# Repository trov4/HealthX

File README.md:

# HealthX
The Health X repository storing all code for the project

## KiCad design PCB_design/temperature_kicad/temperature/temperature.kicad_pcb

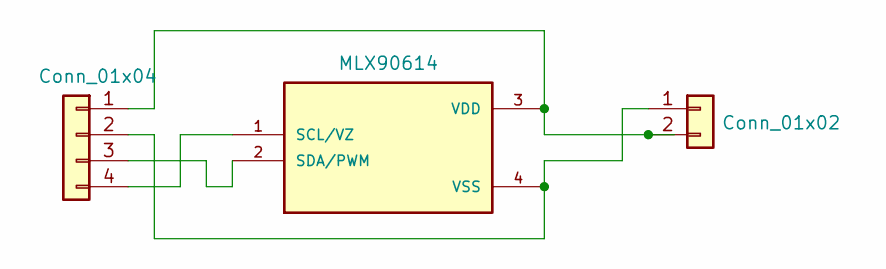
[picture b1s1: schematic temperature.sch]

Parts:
J1: Conn_01x04; PinHeader_1x04_P2.54mm_Vertical
J2: Conn_01x02; PinHeader_1x02_P2.54mm_Vertical
U1: MLX90614; TO254P942H425-4; PARTREV 13

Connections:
unnamed: J1.1, J2.2, U1.3 (VDD)
unnamed: J1.2, J2.1, U1.4 (VSS)
unnamed: J1.3, U1.2 (SDA/PWM)
unnamed: J1.4, U1.1 (SCL/VZ)

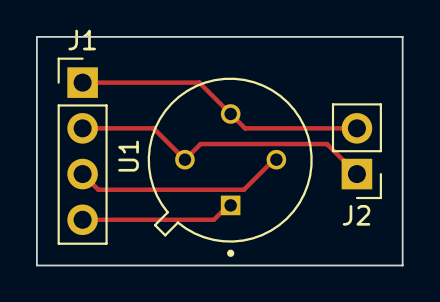
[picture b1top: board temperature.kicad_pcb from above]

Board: 2 copper layers, 20.3 x 12.7 mm, 3 parts (0 on the bottom side), 4 nets.

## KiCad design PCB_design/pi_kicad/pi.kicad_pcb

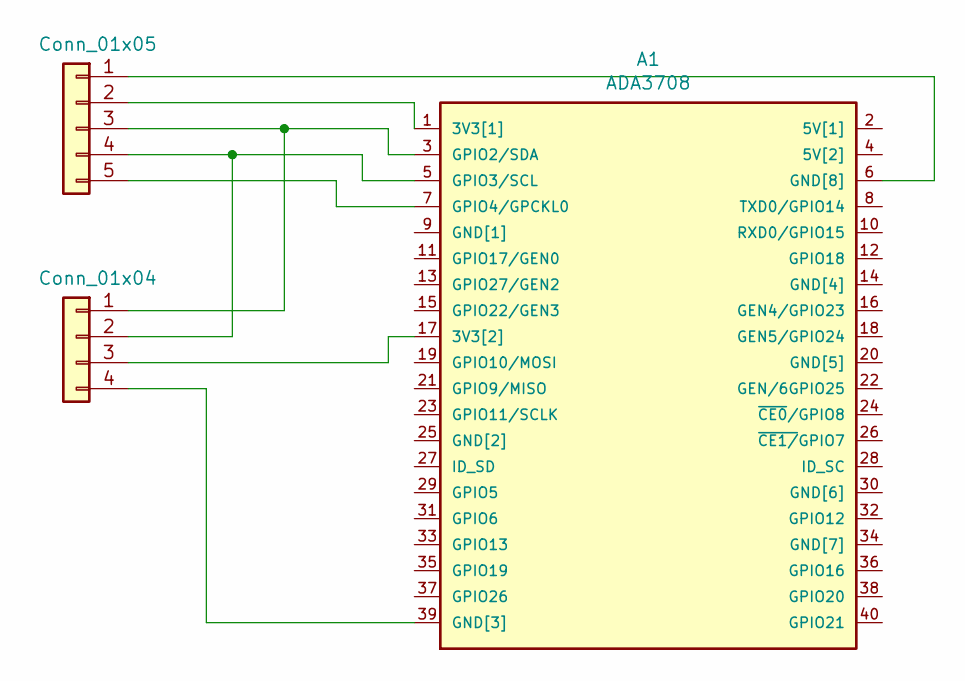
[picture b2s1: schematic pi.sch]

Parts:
A1: ADA3708; ADA3708_RPI-ZERO
J1: Conn_01x05; PinHeader_1x05_P2.54mm_Vertical
J2: Conn_01x04; PinHeader_1x04_P2.54mm_Vertical

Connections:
unnamed: A1.1 (3V3[1]), J1.2
unnamed: A1.3 (GPIO2/SDA), J1.3, J2.1
unnamed: A1.5 (GPIO3/SCL), J1.4, J2.2
unnamed: A1.6 (GND[8]), J1.1
unnamed: A1.7 (GPIO4/GPCKL0), J1.5
unnamed: A1.17 (3V3[2]), J2.3
unnamed: A1.39 (GND[3]), J2.4

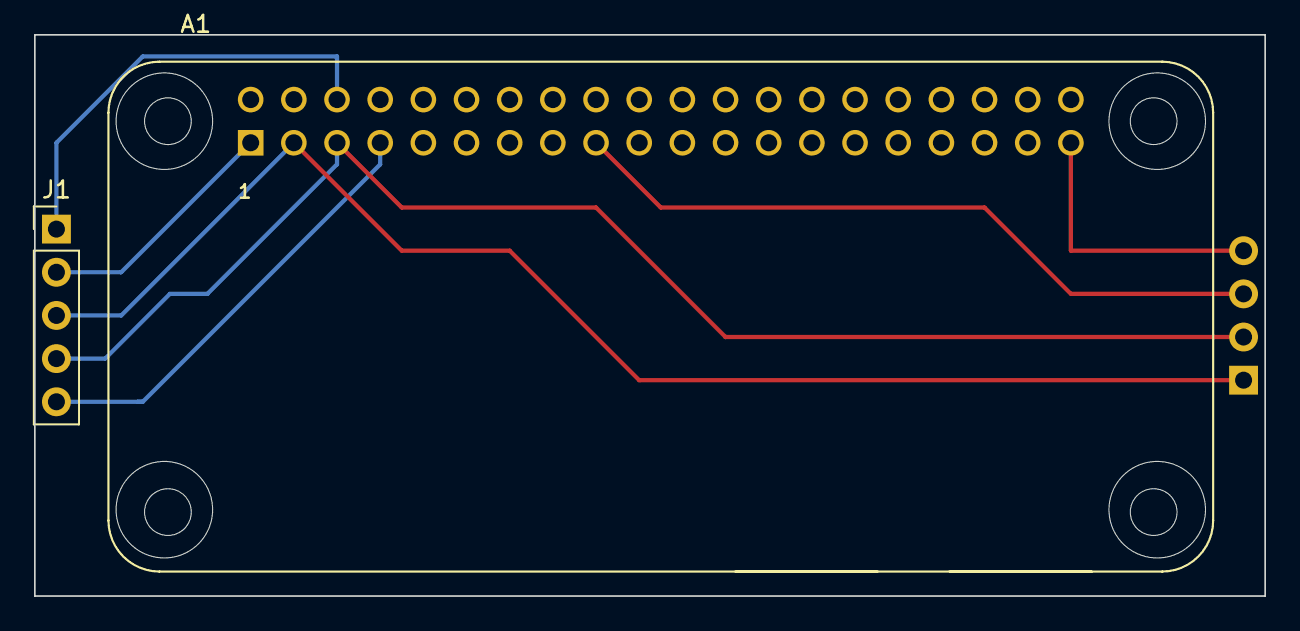
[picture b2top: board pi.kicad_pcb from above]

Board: 2 copper layers, 72.4 x 33.0 mm, 3 parts (1 on the bottom side), 7 nets.

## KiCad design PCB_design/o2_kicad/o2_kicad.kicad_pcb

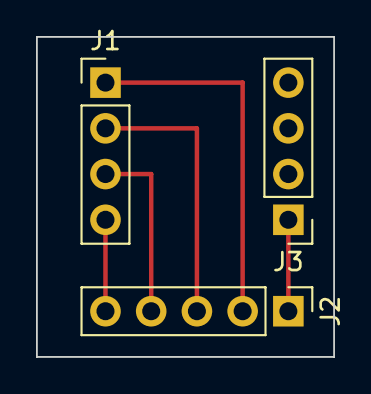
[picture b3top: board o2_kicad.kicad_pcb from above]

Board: 2 copper layers, 16.5 x 17.8 mm, 3 parts (0 on the bottom side), 5 nets.

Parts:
J1, J3: Conn_01x04; PinHeader_1x04_P2.54mm_Vertical
J2: Conn_01x05; PinHeader_1x05_P2.54mm_Vertical

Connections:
unnamed: J1.1, J2.2
unnamed: J1.2, J2.3
unnamed: J1.3, J2.4
unnamed: J1.4, J2.5
unnamed: J2.1, J3.1

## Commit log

2021-08-26 Initialize project using Create React App
2021-09-16 Create info_getItem
2021-09-16 Create info_deleteItem
2021-09-16 Create info_putItem
2021-09-16 Create sensor_getItem
2021-09-16 Create raspberry_pi local
2021-09-21 Create MQTT Connection
2021-09-21 Rename MQTT Connection to AWS IoT
2021-09-23 added David's sensor work
2021-09-23 ahhhh
2021-09-23 removed testing
2021-09-28 This is my commit message
2021-09-30 adding temp sense stuff
2021-10-07 Create GET API
2021-10-14 moving to pi 0
2021-10-14 changing diretory name
2021-10-14 added new IoT to sensors directory
2021-10-14 packed everything up for iot sending
2021-10-15 New version
2021-10-15 adding pymlx items
2021-10-15 This one Trevor
2021-10-15 This one two
2021-10-18 Update GET API
2021-10-28 This is my most recent version
2021-10-28 added rfid submodule
2021-10-28 bump rfid
2021-10-28 This is cert
2021-10-28 IoT updates: RFID connected to AWS
2021-11-16 bump gen2
2021-11-18 The data check done
2021-12-09 Update and rename sensor_getItem to sensor_get_func
2021-12-09 Update info_putItem
2021-12-09 updates from demo
2021-12-09 added pcb
2021-12-09 Create loc_get_func
2021-12-09 Update loc_get_func
2021-12-09 Update sensor_get_func
2021-12-10 added Jiwoo's stuff
